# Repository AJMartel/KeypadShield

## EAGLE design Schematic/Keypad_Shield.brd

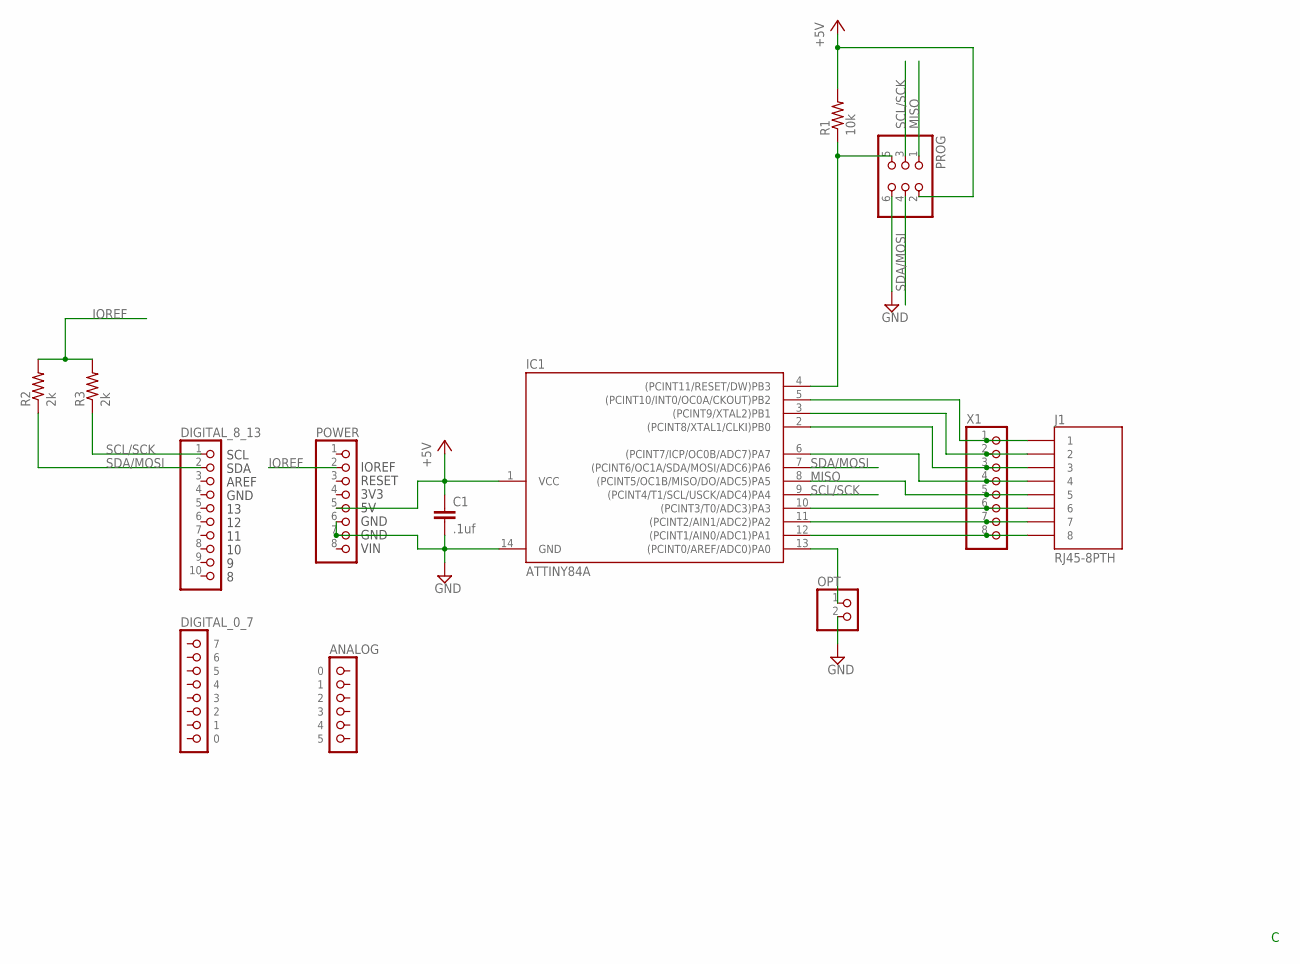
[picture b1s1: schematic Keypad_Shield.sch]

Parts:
C1: .1uf; C5B5
DIGITAL_8_13: PINHD-1X10; 1X10
IC1: ATTINY84A; DIL14
J1: RJ45-8PTH; RJ45-8
OPT: PINHD-1X2; 1X02
POWER: PINHD-1X8; 1X08
PROG: PINHD-2X3; 2X03
R1: 10k; 0204/5
R2, R3: 2k; 0204/5
U$2: ANALOG; 1X06
U$3: DIGITAL_0_7; 1X08
X1: HEADER-1X8ROUND; 1X08_ROUND

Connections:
+5V: C1.1, IC1.1 (VCC), POWER.5, PROG.2, R1.2
GND: C1.2, IC1.14 (GND), OPT.2, POWER.6, POWER.7, PROG.6
IOREF: POWER.2, R2.2, R3.2
MISO: IC1.8 ((PCINT5/OC1B/MISO/DO/ADC5)PA5), J1.5, PROG.1, X1.5
unnamed: IC1.4 ((PCINT11/RESET/DW)PB3), PROG.5, R1.1
unnamed: IC1.13 ((PCINT0/AREF/ADC0)PA0), OPT.1
unnamed: IC1.5 ((PCINT10/INT0/OC0A/CKOUT)PB2), J1.1, X1.1
unnamed: IC1.3 ((PCINT9/XTAL2)PB1), J1.2, X1.2
unnamed: IC1.2 ((PCINT8/XTAL1/CLKI)PB0), J1.3, X1.3
unnamed: IC1.6 ((PCINT7/ICP/OC0B/ADC7)PA7), J1.4, X1.4
unnamed: IC1.10 ((PCINT3/T0/ADC3)PA3), J1.6, X1.6
unnamed: IC1.11 ((PCINT2/AIN1/ADC2)PA2), J1.7, X1.7
unnamed: IC1.12 ((PCINT1/AIN0/ADC1)PA1), J1.8, X1.8
SCL/SCK: DIGITAL_8_13.1, IC1.9 ((PCINT4/T1/SCL/USCK/ADC4)PA4), PROG.3, R3.1
SDA/MOSI: DIGITAL_8_13.2, IC1.7 ((PCINT6/OC1A/SDA/MOSI/ADC6)PA6), PROG.4, R2.1

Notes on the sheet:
SCL SDA AREF GND 13 12 11 10 9 8
IOREF RESET 3V3 5V GND GND VIN

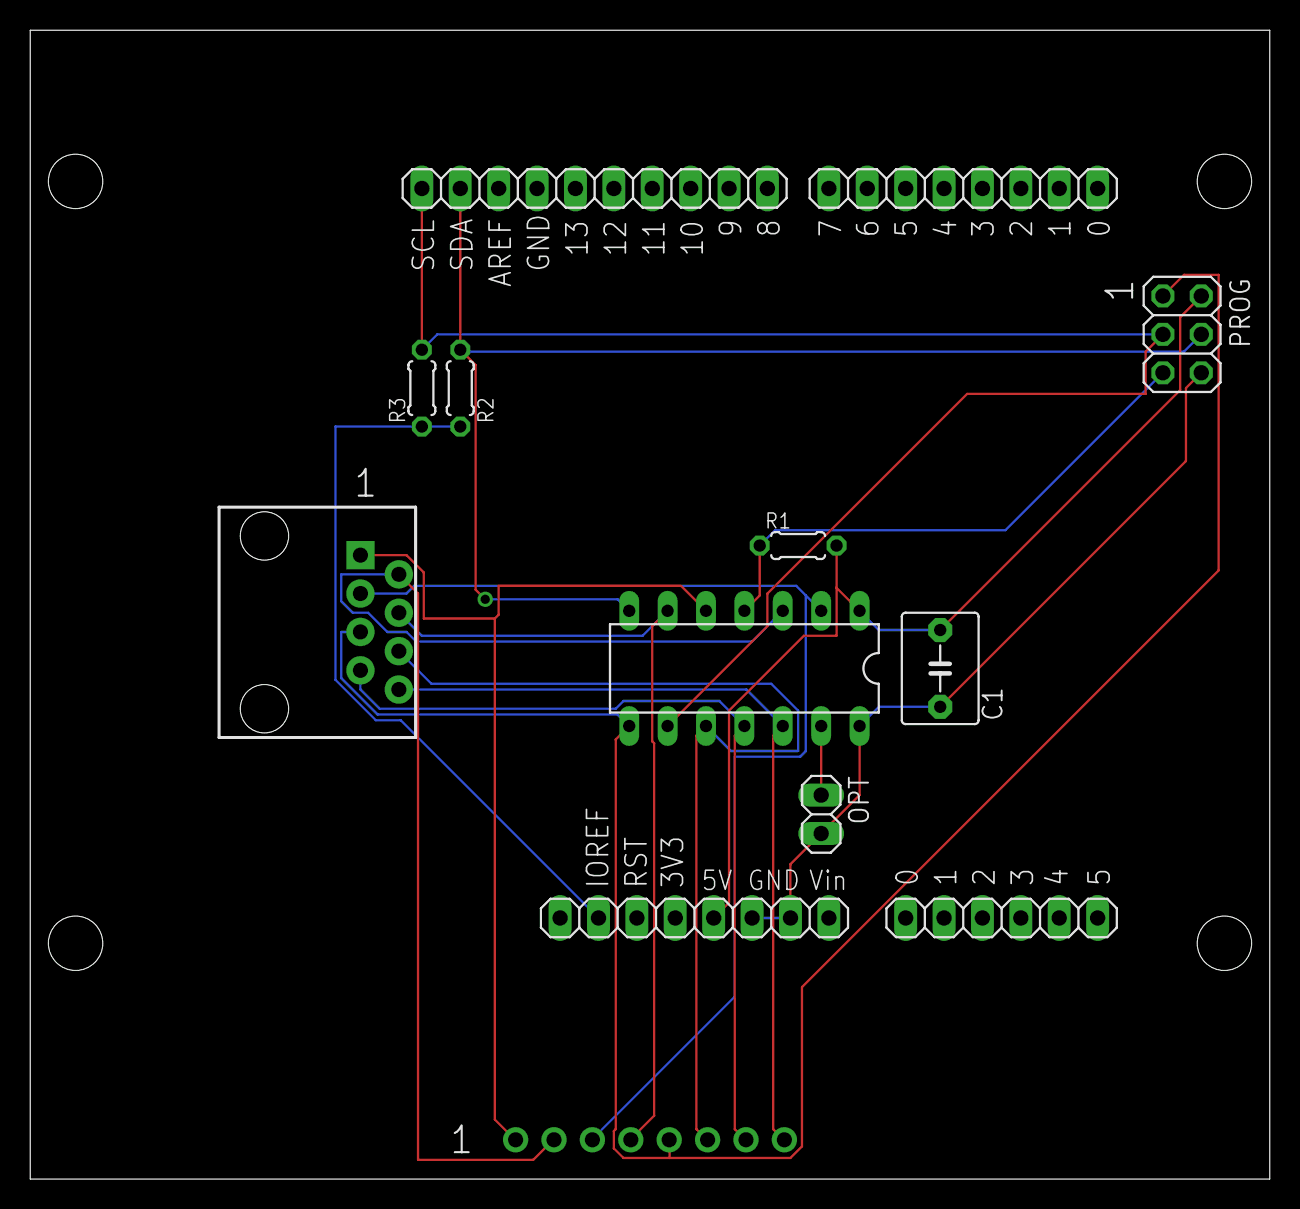
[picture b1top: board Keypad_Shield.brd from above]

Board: 2 copper layers, 82.0 x 76.0 mm, 13 parts (0 on the bottom side), 15 nets.

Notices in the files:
Schematic/Keypad_Shield.brd:
Rev C  Feb 2017  CC BY-SA 4.0
parts and their libraries:
microbuilder: This work is placed in the public domain, and may be freely used for commercial and non-commercial work with the following conditions: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
SparkFun: Licensing: CC v3.0 Share-Alike You are welcome to use this library for commercial purposes.
